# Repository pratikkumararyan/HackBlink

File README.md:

# HackBlink - An Orpheus based Blinky Board!

> [!WARNING]
> ## READ BEFORE CONTINUING
> Read onto the end to see the warning about the .kicad_pcb files. Sorry I don't have a 3D view of the PCB! My potato PC freezes whenever I try to open it, so please enjoy the 2D view only.

---

## SCHEMATIC

### The stasis project validation system wasn't letting my easyeda files thorugh so I used an online converter to convert into a .kicad file, use only the real one tho for pcb! This is because the converted project file doesn't even seem to function properly so remember to use the gerber files only for PCB manufacturing!

---

## A blinky board based on the Hack Club mascot, Orpheus.

---

So I made this project to learn about PCB design and Schematic making as well as to dive into hardware, since I have been doing software only till now and wanna explore the cool world of soldering and hardware too!

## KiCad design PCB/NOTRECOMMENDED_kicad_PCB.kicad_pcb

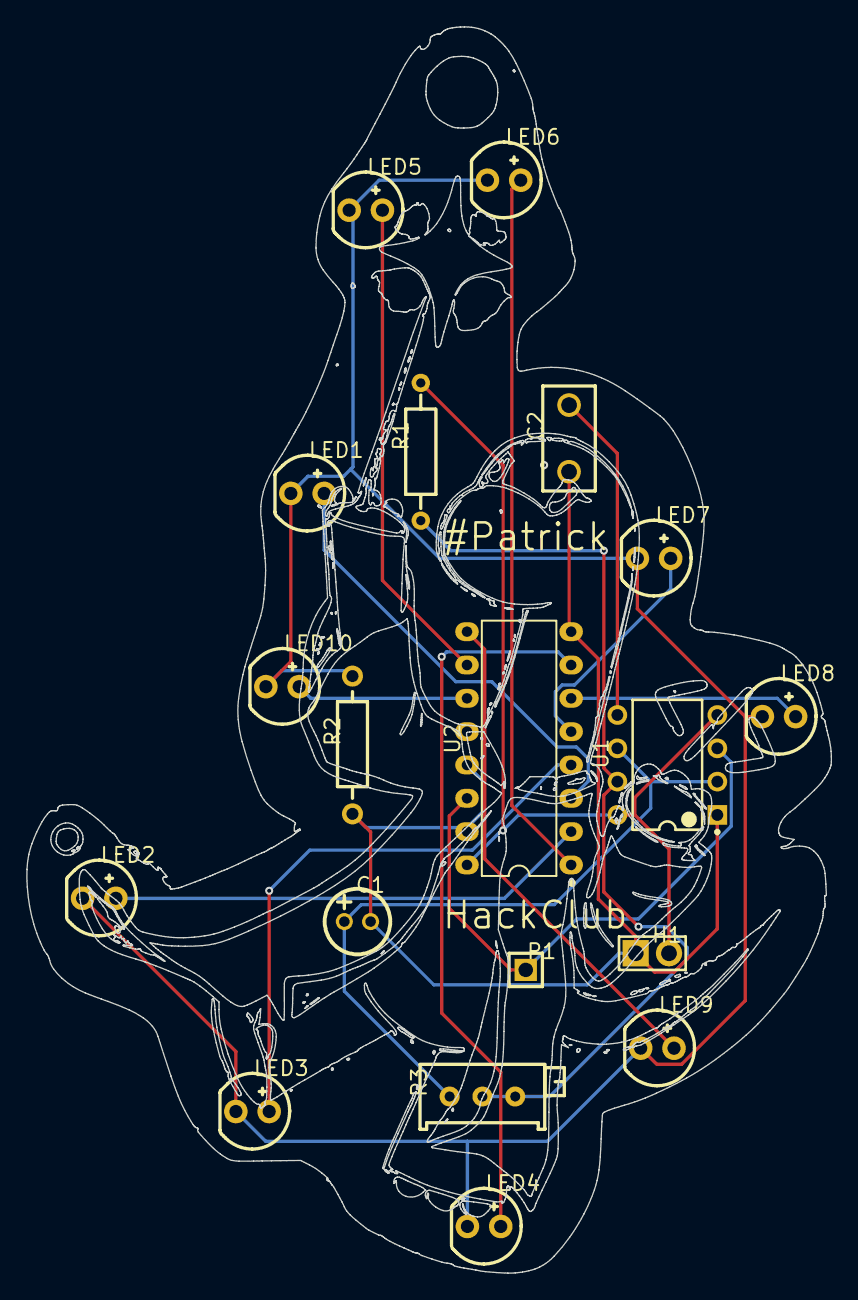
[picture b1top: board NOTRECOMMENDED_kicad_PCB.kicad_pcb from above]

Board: 2 copper layers, 61.3 x 95.0 mm, 19 parts (0 on the bottom side), 17 nets.

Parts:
C1: 1uF; CAP-TH_BD5.0-P2.00-D0.8-FD
C2: 10nF; CAP-TH_L8.0-W4.0-P5.00-D1.2
H1: Header; HDR-TH_2P-P2.54-V-M
LED1, LED2, LED3, LED4, LED5, LED6, LED7, LED8, LED9, LED10: XL-502UWC; LED-TH_BD5.9-P2.54-RD_WHITE
P1: Header-Male-2.54_1x1; HDR-TH_1P-P2.54-V-M
R1: 1kΩ; RES-TH_BD2.3-L6.5-P10.50-D0.5
R2: 470Ω; RES-TH_BD2.2-L6.5-P10.50-D0.6
R3: 50kΩ; RES-ADJ-TH_3P-L9.5-W4.85-P2.50-BL-L
U1: 100kHz; DIP-8_L9.8-W6.6-P2.54-LS7.6-BL
U2: CD4017BE(LX); PDIP-16_L19.3-W6.4-P2.54-LS7.94-BL

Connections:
R2_2: LED1.1, LED2.1, LED3.1, LED4.1, LED5.1, LED6.1, LED7.1, LED8.1, LED9.1, LED10.1, R2.2
U1_1: C1.2, C2.1, H1.1, R2.1, U1.1, U2.8, U2.13, U2.15
U1_2: C1.1, R3.1, U1.2, U1.6
U1_3: P1.1, U1.3, U2.14
U1_4: H1.2, R1.2, U1.4, U1.8, U2.16
U1_5: C2.2, U1.5
U1_7: R1.1, R3.2, R3.3, U1.7
U2_1: LED6.2, U2.1
U2_2: LED2.2, U2.2
U2_3: LED1.2, U2.3
U2_4: LED3.2, U2.4
U2_5: LED7.2, U2.5
U2_6: LED8.2, U2.6
U2_7: LED4.2, U2.7
U2_9: LED9.2, U2.9
U2_10: LED5.2, U2.10
U2_11: LED10.2, U2.11

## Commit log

2026-04-17 Rename Gerber_HackBlink_PCB_HackBlink_2026-04-16.zip to Gerber_HackBlink_PCB.zip
2026-04-17 Rename PCB_PCB_HackBlink_2026-04-16 (2).kicad_pcb to NOTRECOMMENDED_kicad_PCBkicad_pcb
2026-04-17 Rename PCB_PCB_HackBlink_2026-04-16.json to PCB_easyEDA.json
2026-04-17 Rename PCB_PCB_HackBlink_2026-04-16.pdf to PCB2d.pdf
2026-04-17 Rename image (1).png to 2dPCB.png
2026-04-17 Rename NOTRECOMMENDED_kicad_PCBkicad_pcb to NOTRECOMMENDED_kicad_PCB.kicad_pcb
2026-04-17 Final Commit for HackBlink
